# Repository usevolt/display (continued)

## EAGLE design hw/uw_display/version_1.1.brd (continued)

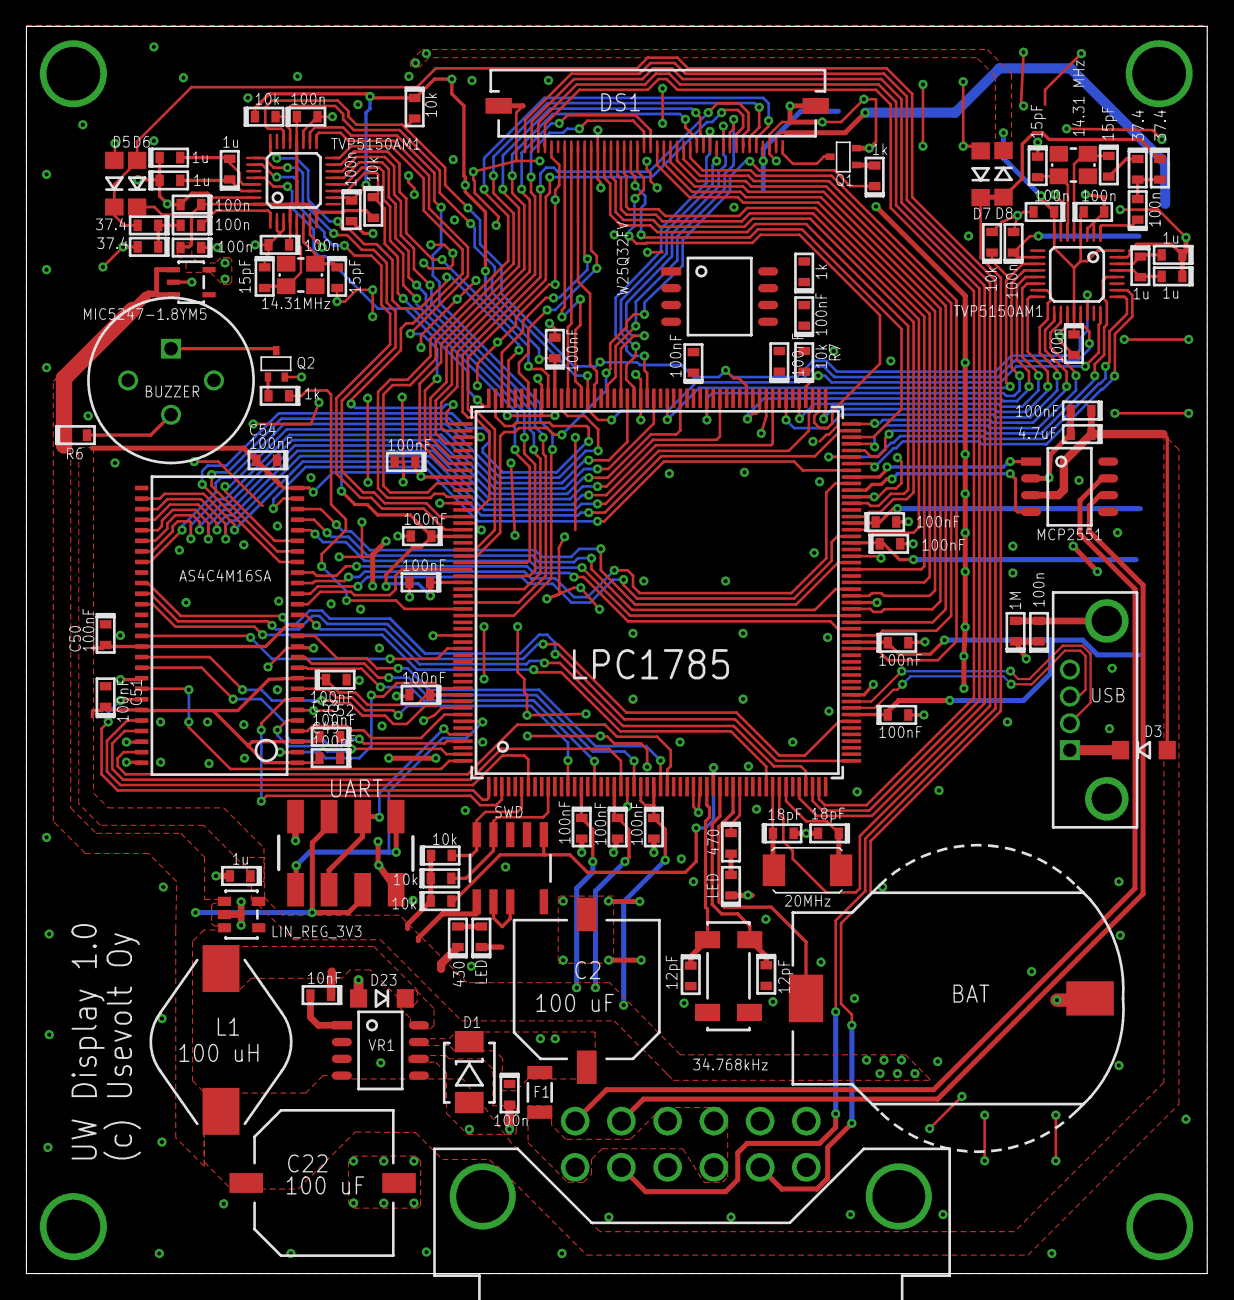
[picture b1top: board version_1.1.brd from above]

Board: 2 copper layers, 89.4 x 94.4 mm, 106 parts (0 on the bottom side), 154 nets.

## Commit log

2016-02-07 Add initial HW files
    - HW files includes version 1.0 & 1.1 eagle files
2016-02-23 Move doc directory from hw to root
2016-03-17 Start developing the display SW
    - Testing freertos
    - UART, timers and gpios are working
    - Add uGUI library to ui directory
2016-04-05 Display runs now with uw_bootloader
2016-04-05 HAL library is linked via git submodule
2016-04-30 Creating interface for external memory
2016-07-04 implementing the EMC interface, not ready yet
2016-07-04 HAL library changed from uw to uv
2016-08-15 Corrected HW connector bolt sizes
2016-08-15 back enclosure bolt hole sizes reduced
2016-09-01 revision 2 pcb ordered from itead
2016-09-07 PCB was too big for itead, reduced size and ordered one
2016-09-12 testing with hard fault
2016-10-02 windows and texts working in UI
2016-10-02 Changed LCD interface from RGB888 to RGB565
2016-10-17 HW revision 3 ordered from itead
2016-10-24 Project changed to use Usevolt makefile
2016-10-28 building the UI: brightness and volume sliders in settings
2016-10-28 release -build-directory excluded from the repository
2016-10-30 oil & fuel level, temperature bars added to taskbar
2016-10-31 Version 4 ordered from shapeways
2016-11-22 can implementing...
2016-12-25 uw180s & uw50 setting pages created
2016-12-31 Almost working version
2017-01-02 first working version
2017-01-04 HAL submodule uses usevolt server as remote
2017-01-04 Removed UI library from project as useless
2017-01-10 snapping connectors for front enclosure
2017-01-20 creating logging interface. Not tested
2017-01-23 Implementing notifications. not tested!
2017-02-01 back encolosure tightning
2017-02-01 enclosure front screw holes widened
2017-02-01 enclosure front screw holes deepened
2017-02-04 working log interface
2017-02-07 heater implemented
2017-02-07 system default values updated
2017-02-17 added snapping interfaces to enclosure
2017-02-17 Created builds for FM and LM
2017-02-22 multiple bug fixes, uv terminal SDO interface
2017-02-22 Rewriting CANopen hal module for improved portability
2017-02-24 small and simple log length variation added
2017-03-13 updated to uv_hal canopen v2
2017-03-13 emergency button implemented
2017-03-14 volume slider removed
2017-03-16 added engine light, emcy stop, LM implementations
2017-03-20 Reading gear from ECU TXPDO 3
2017-03-29 rpm & hydr pressure made global
2017-03-29 merging to old keypads
2017-04-03 uiwindow scrollbar testing
2017-04-04 keypad calibration implemnted, not tested
2017-04-12 corrected keypad calibration bugs
2017-04-12 LM build: Default implement set to UW100, drive back valve removed
2017-04-14 starting to design hw 5.0, with variable current source for LCD backlight
2017-04-16 implementing treeview for settings. Not ready!
2017-04-18 still implementing treeview, not ready
2017-04-18 LM_6.0.1 mods:
    heater canopen messages adjusted
    drive front speeds multiplied by 2
    gui backlight points inreased dramatically
2017-04-20 implementing uitreeview
2017-04-30 hw 1.5.0 ordered
2017-05-06 implementing uitreeview for general setting
2017-05-12 fm build updated to stepless ui init functions
2017-05-14 LM build for std driving valves (2 x LUDV)
2017-05-21 crp removed
2017-05-21 FM drive speed parameters multiplied by 2
2017-05-21 style fix: Unnecessary #if removed
2017-05-21 FM wheels feed max speed multiplied by 2
2017-05-24 settings general tab works again
2017-06-02 Combi Master build added
2017-06-03 CM modifications to alve names etc
2017-06-25 version control bug: pwr_supply_sheet now has fuse for LCD as in hw 1.5.0
2017-06-25 hw version 1.6.0
    * LCD backlight remains off while booting
    * BUZZER amplifying MOSFET circuit changed to low side driving
2017-06-27 small modifications to schematic
2017-07-04 decided to rewrite uitreeview so that uitreeobjects are the dynamic elements
2017-07-07 driving when legs down trigger warning
2017-07-07 valve default parameters adjusted
2017-07-07 default lcd brightness set to 80%
2017-07-07 boom lift, fold, uw180s saw, rotator default speeds adjusted
2017-07-09 bug fix: UW180s log len updated to ECU automatically
2017-07-12 bash script for taking screenshots created
2017-07-18 base machine valves, general settings & system diagnostics changed to uitreeview based
2017-07-18 new orange background colouring adjusted
2017-07-18 bug fix: cm & lm taskbar buffer was too short
2017-07-19 enclosure2 ready to order from shapeways
2017-08-07 hoil tempwarning limit increased to 85 c
2017-08-09 oil temperature warning increased to 80 c
2017-08-12 uw50 saw max speed multiplied by 2 in network: ecu.c
2017-08-20 hour calculator changed to minute counting
2017-08-30 msb heater as in old (0-2 speed)
2017-10-01 enclosure2 ampseal p pocket bugfix
2017-10-24 manual layout improved
2017-10-28 system network tab has data for FSB, ESB & CSB
2017-11-03 working revision with FSB, CSB & ESB
2017-11-15 implementing a multilinguality
2017-11-16 porting uv0a_hds pcb to uw_display
2017-11-20 1.7.0 pcb created, not yet ordered
2017-11-22 old enclosure files removed
2017-11-27 uw180s grab times adjustable
2017-12-10 default engine power usage set to 36
2017-12-19 hw 2.1.0 with LPC1549 & FT812 ordered from seeed
2017-12-19 2.1.0 schematic updates committed
2017-12-23 stencil gerber fixed (solder mask layer changed to solder paste layer
2018-01-23 unknown modifications to hw
2018-01-26 260117 Iceland: adding new users work, can error frames decreased
2018-01-26 valve default parameters set to fit LM_6.1.2
2018-01-27 unnecessary disconnected-warnings removed
2018-01-30 enclosure2_back bug fies
2018-02-05 FM_6.6.1 working revisioN
2018-02-16 uw180s mb min & max calibration buttons added
2018-02-24 heater & wiper moved to taskbar
2018-02-26 FM_6.4.1 new display sent 260218
2018-03-04 hour counter duplexed with ESB
2018-03-12 heater and wiper in taskbar, mb volume measurement working
2018-03-26 csb wiper request implemented
2018-03-28 ergo (fm_6.6.2) bug fix: display couts hours correctly.
2018-03-28 hour counter 32 bit value
2018-04-02 multilingual english & finnish implemented
2018-04-02 wiper logic reverted to previos version: display sets the wiper speed directly
2018-04-07 bug fixes when moving engine power usage to esb
2018-04-14 FM_6.5.1: uw180s mb nodeid 0xF
2018-04-19 kicad schematic update
2018-04-19 190418: disconnected and can bus alerts removed
2018-04-20 volume and width removed from uw180s dashboard
2018-05-04 040518: oil cooler trigger temp is remembered
2018-05-04 oilcooler trigger temp added to user data
2018-05-04 040518: oil cooler trigger temp is saved in display
2018-05-06 050518: icu interface for kikepera proto head
2018-05-29 working rtc module for LPC1549
2018-06-03 gerber files added to zip archive
2018-06-04 030618: seat switch implemented in ecu
2018-06-05 width measurement enabled, dirve max speed multiplied by 2
2018-06-06 060618: first working portotype, ready for testing in forest
2018-06-09 motor temp warning limit increased to 96 deg
2018-06-27 blades & rollers grab time settings added
2018-07-12 120718: kikepera harvester head widtha dn volume measurement
2018-08-14 log warnings disabled, motor temp warning increased
2018-08-15 140818: ESB, FSB, CSB added, display and ECU unmodofied
2018-08-29 compiles without lpcxpresso
2018-09-01 cr_section _macros removed
2018-09-01 asdasd
2018-09-01 010918: ads
2018-09-02 trying to get working with licr
2018-09-02 020918: added oilcooler trigget temp value
2018-09-09 CM_6.2.1 delivered, first customer machine with CCU, HCU & ICU
2018-09-13 network update disable implemented
2018-09-13 hal updated
2018-09-14 130918: working with kubota 1505T
2018-09-18 bugfixes in valve assembly invert settings
2018-10-14 141018: trying to build project withouth external linkage to NXP libraries
2018-10-14 141018: now compiles
2018-10-14 code red libraries added to hal display_master branch
2018-11-02 rollers grab time bugfix
2018-11-05 bugfix: ccu drive 2&3 speeds can be read in system network
2018-11-13 CM_6.2.1 released
2019-01-02 valve default currents modified to aaply with real currents
2019-01-21 deleted old lcd panel datasheet
2019-02-09 weird modifications
2019-02-10 pressing heater from taskbar toggles between on/off
2019-02-19 implementing user copy button, not yet tested
2019-02-25 tilt float added to uw180s settings
2019-03-16 uw180s tilt valve conf step decreased
2019-03-25 driving compensation added
2019-06-03 back steering implemented
2019-07-29 hydrout implement added
2019-07-29 bugfix: hydout valve settings are updated when implement is changed
2019-08-10 brightness req added to canopen interface
2019-08-22 version control changed to github
2019-08-23 impl2 valve is usable with uw100, usaful with skidding grapple
2019-10-09 submodule urls set to https github
2019-10-30 uw180s length target can be changed with right but3
2019-11-15 German translation replaced with swedish translations
2019-11-17 bugfix: drive compensation unsigned values changed to signed
2019-11-19 UW180s: tilt on thumb setting added
2019-11-29 swedish manual created
2019-12-14 radiator enable togglebutton added
2019-12-15 131219: radiator disable button added, valve default min values adjusted
2019-12-22 uw180s width measurement made easier: only min_mm and max_mm are required
2019-12-30 implementing tcu
2019-12-30 uw180s manual translations send
2020-01-02 TCU ready for first prototype tests
2020-01-02 020120: TCU interface implemented but reverted back old uw180s width calib
2020-01-02 021220: TCU telescope buttons revmoed
2020-01-02 TCU telescope buttons removed, controlled by lkeyboard
2020-01-17 ui glitch fix with kubota lights in taskbar
2020-01-18 taskbar hours ui glitch fix
2020-02-01 bugfixes: params are saved accross the network when operator changes, ccu telescope and backsteer params are udpated on op change only if they are enabled
2020-02-01 op change save parameters _after_ setting the params
2020-02-08 estonian manual added
2020-02-12 factory reset removed from boot up if display was pressed
2020-03-22 complies
2020-05-17 impl1 & impl2 are updated when changing to uw180s
2020-05-17 also rotator valve is updated when changing the implemen
2020-05-18 blades grab time removed from ui as deprecated
2020-05-19 icu uploads correct log length on start up
2020-05-19 updateing
2020-05-19 190520: updated drive compensation and faster display
2020-05-19 taskbar engine ligths glitch fix
2020-07-07 CCU AIN1&2 IMPL2 control implemented
2020-07-20 MTEMP warning limit increased to 105 deg
2020-07-20 enclosure files moved to enclosre directionry
2020-07-20 enclosure directory moved to root
2020-07-20 displa pcb reverted back to 1.6.0 revision and imporved to 1.7.0
2020-08-04 040820: drive back valve settings added
2020-08-04 040820: sensors are once again working
2020-08-05 mtemp bar limit is set only if water temp sensor triggers
2020-08-21 valve default speeds modified
2020-08-21 tilt on left thumb button removed
2020-08-21 add_user button removed from login
2020-09-05 converting mb nodeid back to default 0xD
2020-09-05 050920: mb nodeid set to default 0xD
2020-10-28 fsb heater speed renewed with cold air
2020-10-28 swedish translations updated according to Anders
2020-12-28 work rpm req implemented for stage5 engine
2020-12-30 heater speed color update
2021-01-04 stage 4 kubota version
2021-03-13 network bugfix
2021-04-09 display.json added
2021-06-04 taskbar heater speed bugfix
2022-06-28 drivedirection shown on gear
2024-04-08 tomi kuusisto alertsa removed from taskbar, double buffering disabled
2024-08-05 240805: alerts really removed, temp sensor scales increased
2025-12-10 j1939 force regen button added
